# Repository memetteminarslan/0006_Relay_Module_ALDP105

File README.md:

# 0006_Relay_Module_ALDP105

You are seeing a large number of widely used Relay modules in electronic development kits. More information coming soon...

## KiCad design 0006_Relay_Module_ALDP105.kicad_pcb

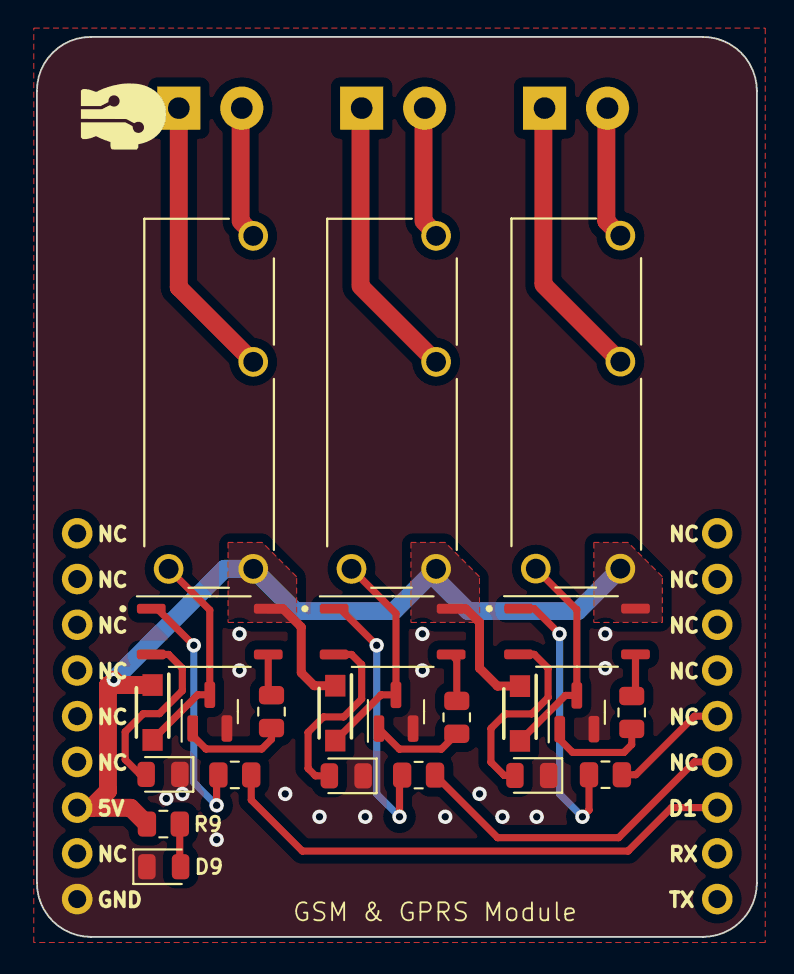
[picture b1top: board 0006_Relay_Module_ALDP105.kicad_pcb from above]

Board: 2 copper layers, 40.0 x 50.0 mm, 27 parts (0 on the bottom side), 27 nets.

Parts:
D1, D2, D3, D9: LED; LED_0805_2012Metric
D5, D6, D7: 1N5819W; SODFL3618X110N
J1, J2, J3: Screw_Terminal_01x02; TerminalBlock_4Ucon_1x02_P3.50mm_Horizontal
K1, K2, K3: ALDP105W; RELAY_ALDP105W
Q1, Q2, Q3: BC817; SOT-23
R1, R2, R3: 220r; R_0805_2012Metric
R5, R6, R7: 1k; R_0805_2012Metric
R9: R; R_0805_2012Metric
U1, U2, U3: TLP185; SOIC-4_4.55x3.7mm_P2.54mm
U4: air__module

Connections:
+5V: D5.1 (K), D6.1 (K), D7.1 (K), K1.1, K2.1, K3.1, R9.1, U1.6, U2.6, U3.6, U4.7 (5V)
GND: D1.1 (K), D2.1 (K), D3.1 (K), D9.1 (K), Q1.2 (E), Q2.2 (E), Q3.2 (E), U4.9 (GND)
unnamed: D1.2 (A), U1.3
unnamed: D2.2 (A), U2.3
unnamed: D3.2 (A), U3.3
unnamed: D5.2 (A), K2.2, Q2.3 (C)
unnamed: D6.2 (A), K1.2, Q1.3 (C)
unnamed: D7.2 (A), K3.2, Q3.3 (C)
unnamed: D9.2 (A), R9.2
unnamed: J1.1, K1.3
unnamed: J1.2, K1.4
unnamed: J2.1, K2.3
unnamed: J2.2, K2.4
unnamed: J3.1, K3.3
unnamed: J3.2, K3.4
unnamed: Q1.1 (B), R5.2
unnamed: Q2.1 (B), R6.2
unnamed: Q3.1 (B), R7.2
unnamed: R1.2, U1.1
unnamed: R2.2, U2.1
unnamed: R3.2, U3.1
unnamed: R5.1, U1.4
unnamed: R6.1, U2.4
unnamed: R7.1, U3.4
R1: R1.1, U4.12 (GPIO)
R2: R2.1, U4.13 (GPIO)
R3: R3.1, U4.14 (GPIO)
